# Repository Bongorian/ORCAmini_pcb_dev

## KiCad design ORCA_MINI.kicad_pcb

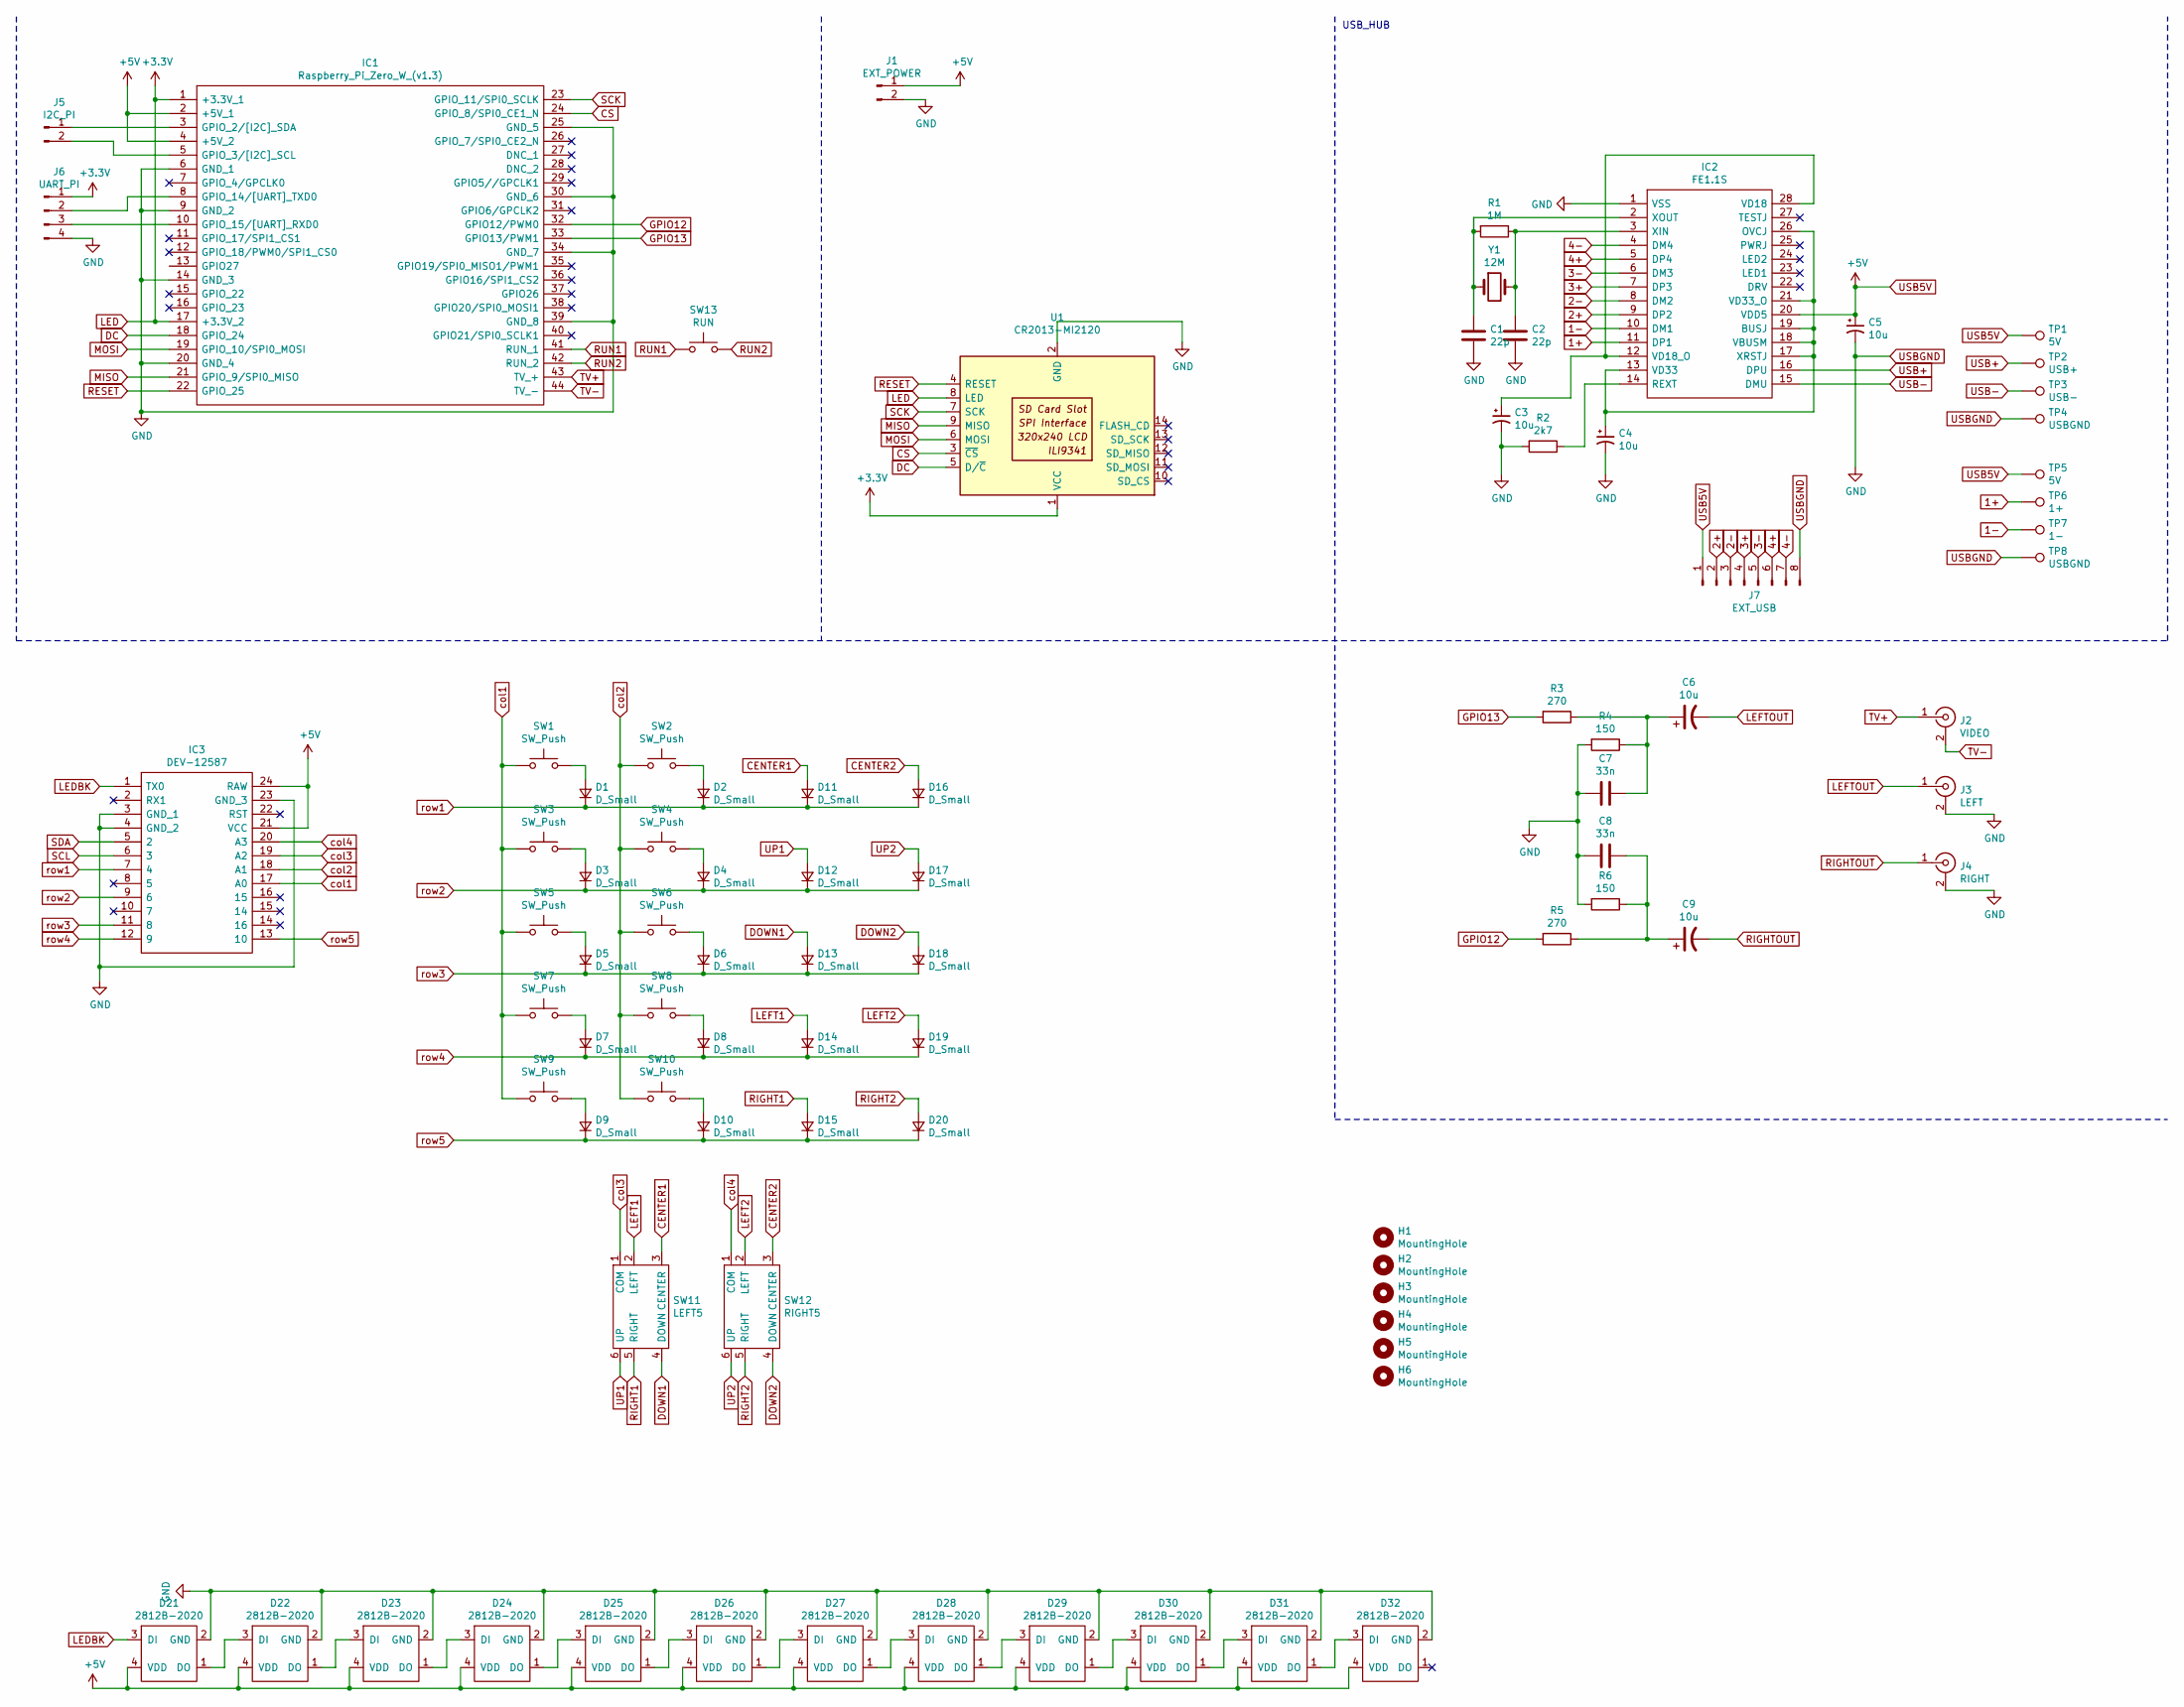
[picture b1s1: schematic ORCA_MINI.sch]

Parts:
C1, C2: 22p; C_0805_2012Metric_Pad1.15x1.40mm_HandSolder
C3, C4, C5: 10u; C_0805_2012Metric_Pad1.15x1.40mm_HandSolder
C6, C9: 10u; CP_Radial_D5.0mm_P2.00mm
C7, C8: 33n; C_Disc_D4.3mm_W1.9mm_P5.00mm
D1, D2, D3, D4, D5, D6, D7, D8, D9, D10, D11, D12, D13, D14, D15, D16, D17, D18, D19, D20: D_Small; D_T-1_P5.08mm_Horizontal
D21, D22, D23, D24, D25, D26, D27, D28, D29, D30, D31, D32: 2812B-2020
H1, H2, H3, H4, H5, H6: MountingHole; MountingHole_2.7mm_M2.5
IC1: Raspberry_Pi_Zero_W_(v1.3); RASPBERRYPIZEROWV13; Manufacturer_Part_Number Raspberry Pi Zero W (v1.3)
IC2: FE1.1S; SSOP-28_3.9x9.9mm_P0.635mm; Manufacturer_Part_Number FE1.1S
IC3: DEV-12587; DIPS1525W55P254L3325H1250Q24N; Manufacturer_Part_Number DEV-12587
J1: EXT_POWER; JST_XH_B02B-XH-A_1x02_P2.50mm_Vertical
J2: VIDEO; RCA_RJ2410N
J3: LEFT; RCA_RJ2410N
J4: RIGHT; RCA_RJ2410N
J5: I2C_PI; PinHeader_1x02_P2.54mm_Vertical
J6: UART_PI; PinHeader_1x04_P2.54mm_Vertical
J7: EXT_USB; JST_SH_BM08B-SRSS-TB_1x08-1MP_P1.00mm_Vertical
R1: 1M; R_Axial_DIN0204_L3.6mm_D1.6mm_P5.08mm_Horizontal
R2: 2k7; R_Axial_DIN0204_L3.6mm_D1.6mm_P5.08mm_Horizontal
R3, R5: 270; R_Axial_DIN0204_L3.6mm_D1.6mm_P5.08mm_Horizontal
R4, R6: 150; R_Axial_DIN0204_L3.6mm_D1.6mm_P5.08mm_Horizontal
SW1, SW2, SW3, SW4, SW5, SW6, SW7, SW8, SW9, SW10: SW_Push; PG1350
SW11: LEFT5; 5WAY_SMD_101009
SW12: RIGHT5; 5WAY_SMD_101009
SW13: RUN; SW_PUSH_6mm
TP1, TP5: 5V; TestPoint_Pad_D1.5mm
TP2: USB+; TestPoint_Pad_D1.5mm
TP3: USB-; TestPoint_Pad_D1.5mm
TP4, TP8: USBGND; TestPoint_Pad_D1.5mm
TP6: 1+; TestPoint_Pad_D1.5mm
TP7: 1-; TestPoint_Pad_D1.5mm
U1: CR2013-MI2120
Y1: 12M; Crystal_HC49-4H_Vertical

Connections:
1+: IC2.11 (DP1), TP6.1
1-: IC2.10 (DM1), TP7.1
2+: IC2.9 (DP2), J7.2
2-: IC2.8 (DM2), J7.3
3+: IC2.7 (DP3), J7.4
3-: IC2.6 (DM3), J7.5
4+: IC2.5 (DP4), J7.6
4-: IC2.4 (DM4), J7.7
CENTER1: D11.2 (A), SW11.3 (CENTER)
CENTER2: D16.2 (A), SW12.3 (CENTER)
CS: IC1.24 (GPIO_8/SPI0_CE1_N), U1.3 (~CS)
DC: IC1.18 (GPIO_24), U1.5 (D/~C)
DOWN1: D13.2 (A), SW11.4 (DOWN)
DOWN2: D18.2 (A), SW12.4 (DOWN)
GPIO12: IC1.32 (GPIO12/PWM0), R5.2
GPIO13: IC1.33 (GPIO13/PWM1), R3.2
LED: IC1.1 (+3.3V_1), IC1.17 (+3.3V_2), J6.1, U1.1 (VCC), U1.8 (LED)
LEDBK: D21.3 (DI), IC3.1 (TX0)
LEFT1: D14.2 (A), SW11.2 (LEFT)
LEFT2: D19.2 (A), SW12.2 (LEFT)
LEFTOUT: C6.2, J3.1 (In)
MISO: IC1.21 (GPIO_9/SPI0_MISO), U1.9 (MISO)
MOSI: IC1.19 (GPIO_10/SPI0_MOSI), U1.6 (MOSI)
unnamed: C1.1, IC2.2 (XOUT), R1.2, Y1.1
unnamed: C2.1, IC2.3 (XIN), R1.1, Y1.2
unnamed: C3.1, IC2.12 (VD18_O), IC2.28 (VD18)
unnamed: C4.1, IC2.13 (VD33), IC2.17 (XRSTJ), IC2.18 (VBUSM), IC2.19 (BUSJ), IC2.21 (VD33_O), IC2.26 (OVCJ)
unnamed: C6.1, C7.1, R3.1, R4.1
unnamed: C8.1, C9.1, R5.1, R6.1
unnamed: D1.2 (A), SW1.2
unnamed: D2.2 (A), SW2.2
unnamed: D3.2 (A), SW3.2
unnamed: D4.2 (A), SW4.2
unnamed: D5.2 (A), SW5.2
unnamed: D6.2 (A), SW6.2
unnamed: D7.2 (A), SW7.2
unnamed: D8.2 (A), SW8.2
unnamed: D9.2 (A), SW9.2
unnamed: D10.2 (A), SW10.2
unnamed: D21.1 (DO), D22.3 (DI)
unnamed: D22.1 (DO), D23.3 (DI)
unnamed: D23.1 (DO), D24.3 (DI)
unnamed: D24.1 (DO), D25.3 (DI)
unnamed: D25.1 (DO), D26.3 (DI)
unnamed: D26.1 (DO), D27.3 (DI)
unnamed: D27.1 (DO), D28.3 (DI)
unnamed: D28.1 (DO), D29.3 (DI)
unnamed: D29.1 (DO), D30.3 (DI)
unnamed: D30.1 (DO), D31.3 (DI)
unnamed: D31.1 (DO), D32.3 (DI)
unnamed: IC1.3 (GPIO_2/[I2C]_SDA), J5.1
unnamed: IC1.5 (GPIO_3/[I2C]_SCL), J5.2
unnamed: IC1.8 (GPIO_14/[UART]_TXD0), J6.2
unnamed: IC1.10 (GPIO_15/[UART]_RXD0), J6.3
unnamed: IC2.14 (REXT), R2.1
RESET: IC1.22 (GPIO_25), U1.4 (RESET)
RIGHT1: D15.2 (A), SW11.5 (RIGHT)
RIGHT2: D20.2 (A), SW12.5 (RIGHT)
RIGHTOUT: C9.2, J4.1 (In)
RUN1: IC1.41 (RUN_1), SW13.1
RUN2: IC1.42 (RUN_2), SW13.2
SCK: IC1.23 (GPIO_11/SPI0_SCLK), U1.7 (SCK)
TV+: IC1.43 (TV_+), J2.1 (In)
TV-: IC1.44 (TV_-), J2.2 (Ext)
UP1: D12.2 (A), SW11.6 (UP)
UP2: D17.2 (A), SW12.6 (UP)
USB5V: C5.1, D21.4 (VDD), D22.4 (VDD), D23.4 (VDD), D24.4 (VDD), D25.4 (VDD), D26.4 (VDD), D27.4 (VDD), D28.4 (VDD), D29.4 (VDD), D30.4 (VDD), D31.4 (VDD), D32.4 (VDD), IC1.2 (+5V_1), IC1.4 (+5V_2), IC2.20 (VDD5), IC3.21 (VCC), IC3.24 (RAW), J1.1, J7.1, TP1.1, TP5.1
USB+: IC2.16 (DPU), TP2.1
USB-: IC2.15 (DMU), TP3.1
USBGND: C1.2, C2.2, C3.2, C4.2, C5.2, C7.2, C8.2, D21.2 (GND), D22.2 (GND), D23.2 (GND), D24.2 (GND), D25.2 (GND), D26.2 (GND), D27.2 (GND), D28.2 (GND), D29.2 (GND), D30.2 (GND), D31.2 (GND), D32.2 (GND), IC1.6 (GND_1), IC1.9 (GND_2), IC1.14 (GND_3), IC1.20 (GND_4), IC1.25 (GND_5), IC1.30 (GND_6), IC1.34 (GND_7), IC1.39 (GND_8), IC2.1 (VSS), IC3.3 (GND_1), IC3.4 (GND_2), IC3.23 (GND_3), J1.2, J3.2 (Ext), J4.2 (Ext), J6.4, J7.8, R2.2, R4.2, R6.2, TP4.1, TP8.1, U1.2 (GND)
col1: IC3.17 (A0), SW1.1, SW3.1, SW5.1, SW7.1, SW9.1
col2: IC3.18 (A1), SW2.1, SW4.1, SW6.1, SW8.1, SW10.1
col3: IC3.19 (A2), SW11.1 (COM)
col4: IC3.20 (A3), SW12.1 (COM)
row1: D1.1 (K), D2.1 (K), D11.1 (K), D16.1 (K), IC3.7 (4)
row2: D3.1 (K), D4.1 (K), D12.1 (K), D17.1 (K), IC3.9 (6)
row3: D5.1 (K), D6.1 (K), D13.1 (K), D18.1 (K), IC3.11 (8)
row4: D7.1 (K), D8.1 (K), D14.1 (K), D19.1 (K), IC3.12 (9)
row5: D9.1 (K), D10.1 (K), D15.1 (K), D20.1 (K), IC3.13 (10)

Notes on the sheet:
USB_HUB

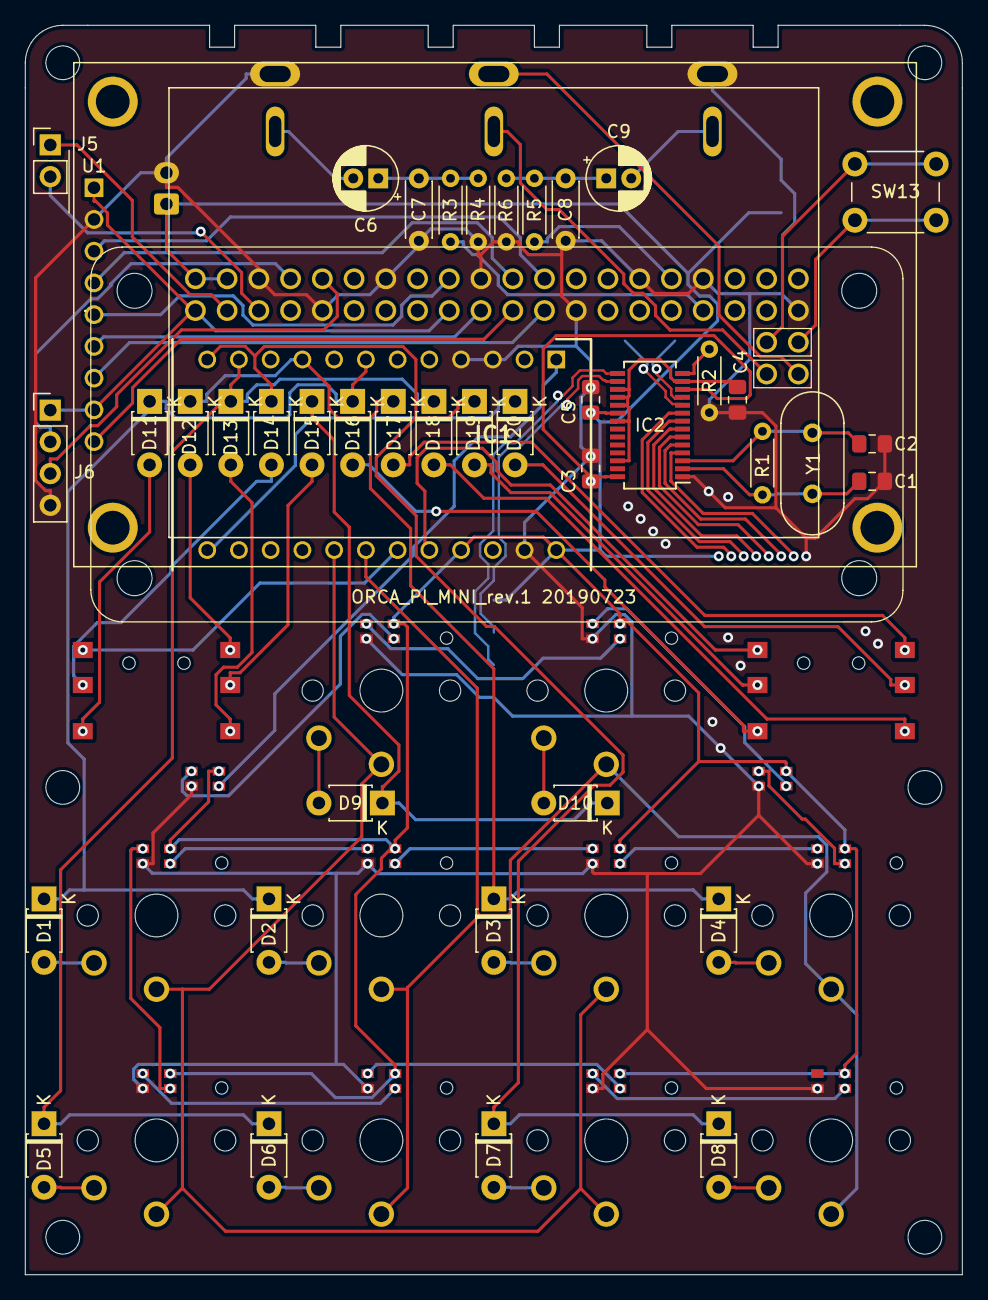
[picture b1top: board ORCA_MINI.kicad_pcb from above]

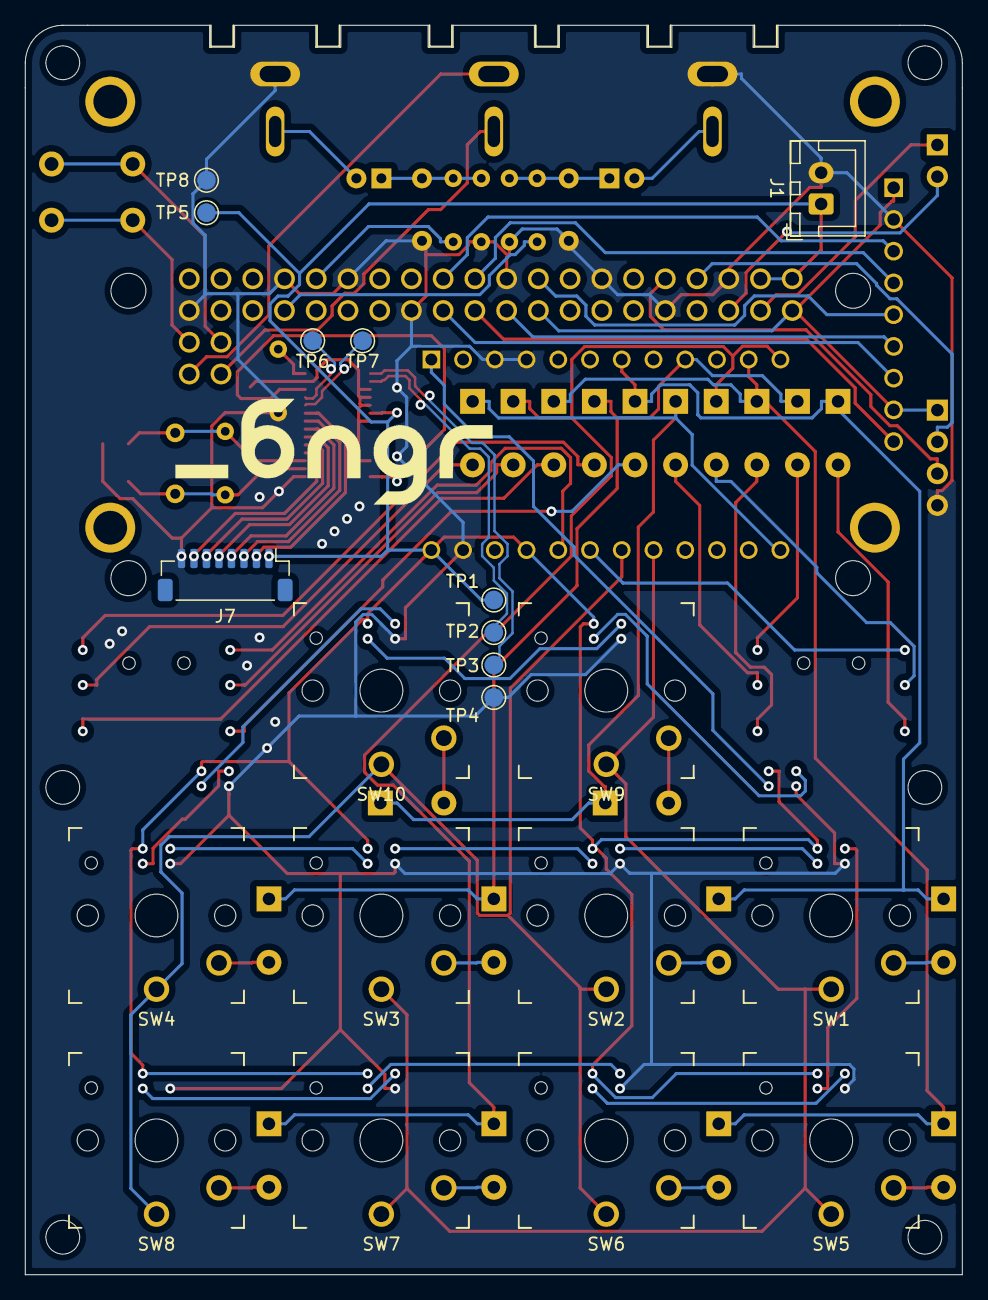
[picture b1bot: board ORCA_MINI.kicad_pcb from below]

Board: 2 copper layers, 75.0 x 100.0 mm, 86 parts (13 on the bottom side), 79 nets.
